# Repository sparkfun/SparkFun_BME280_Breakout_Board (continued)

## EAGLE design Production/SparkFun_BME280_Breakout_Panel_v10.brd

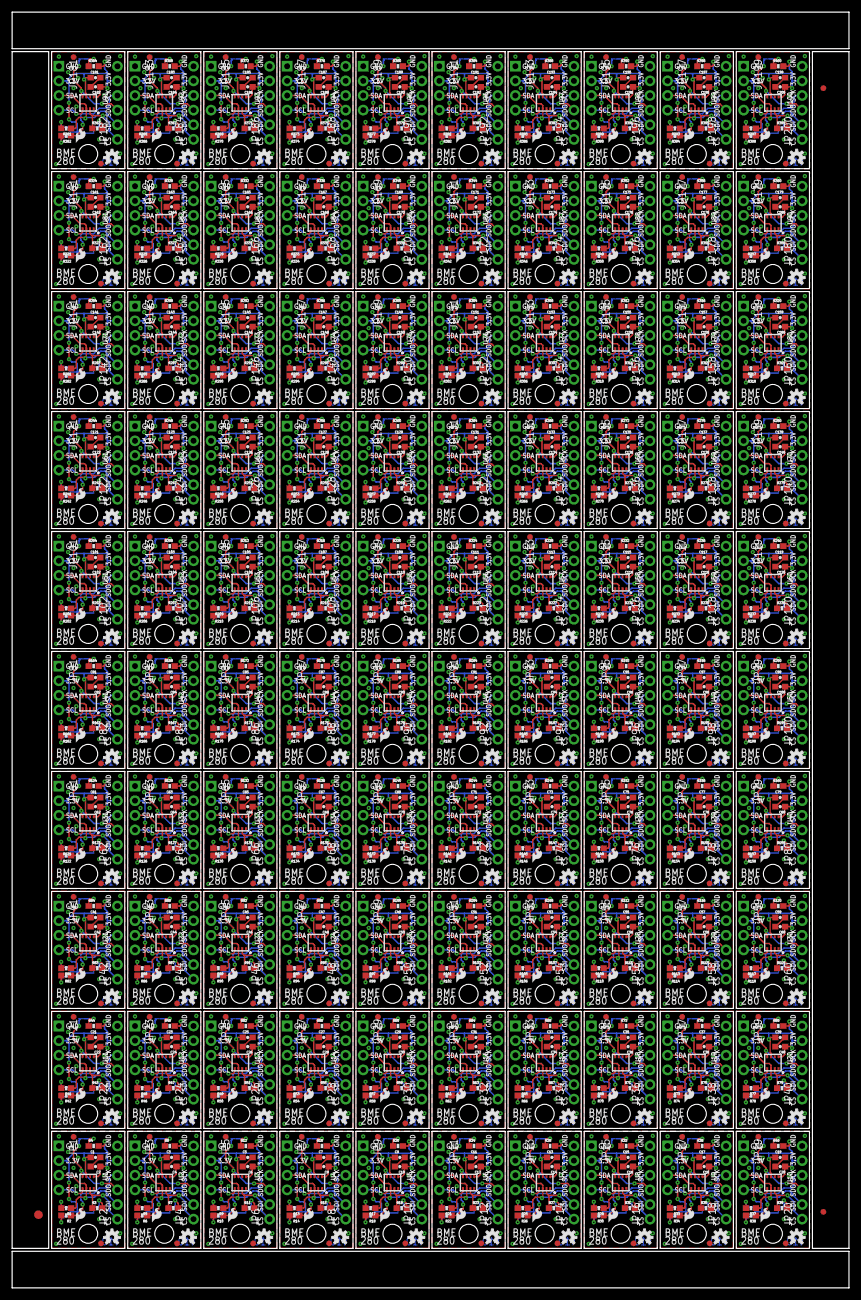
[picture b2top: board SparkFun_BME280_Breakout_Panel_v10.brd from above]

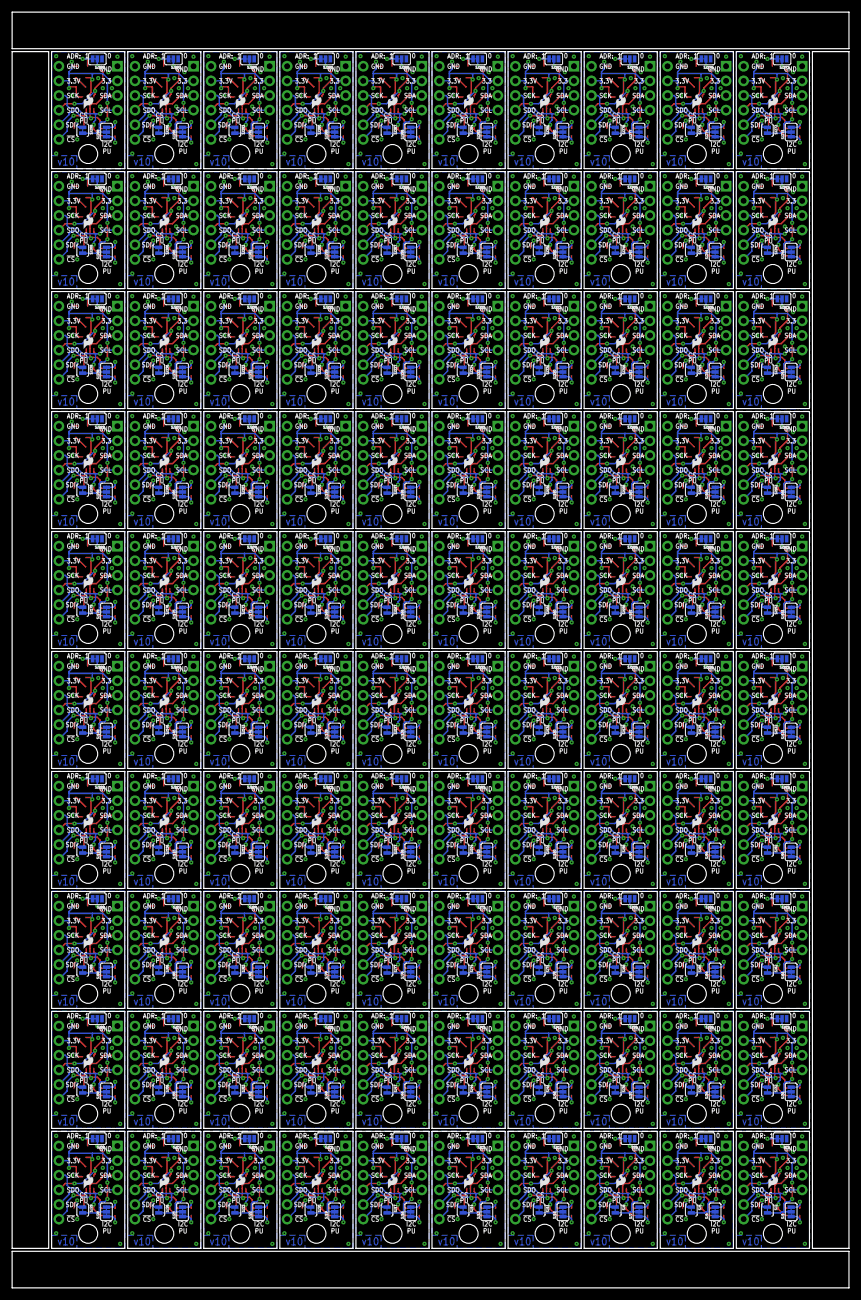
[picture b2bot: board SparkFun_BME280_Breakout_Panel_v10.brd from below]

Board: 2 copper layers, 145.3 x 221.5 mm, 1803 parts (400 on the bottom side), 1000 nets.

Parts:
C1, C2, C3, C4, C5, C6, C7, C8, C9, C10, C11, C12, C13, C14, C15, C16, C17, C18, C19, C20, C21, C22, C23, C24, C25, C26, C27, C28, C29, C30, C31, C32, C33, C34, C35, C36, C37, C38, C39, C40, C41, C42, C43, C44, C45, C46, C47, C48, C49, C50, C51, C52, C53, C54, C55, C56, C57, C58, C59, C60, C61, C62, C63, C64, C65, C66, C67, C68, C69, C70, C71, C72, C73, C74, C75, C76, C77, C78, C79, C80, C81, C82, C83, C84, C85, C86, C87, C88, C89, C90, C91, C92, C93, C94, C95, C96, C97, C98, C99, C100, C101, C102, C103, C104, C105, C106, C107, C108, C109, C110, C111, C112, C113, C114, C115, C116, C117, C118, C119, C120, C121, C122, C123, C124, C125, C126, C127, C128, C129, C130, C131, C132, C133, C134, C135, C136, C137, C138, C139, C140, C141, C142, C143, C144, C145, C146, C147, C148, C149, C150, C151, C152, C153, C154, C155, C156, C157, C158, C159, C160, C161, C162, C163, C164, C165, C166, C167, C168, C169, C170, C171, C172, C173, C174, C175, C176, C177, C178, C179, C180, C181, C182, C183, C184, C185, C186, C187, C188, C189, C190, C191, C192, C193, C194, C195, C196, C197, C198, C199, C200: 0.1uF; 0603-CAP
E$1: FIDUCIAL-1.5X3
E$5, E$6: FIDUCIAL-1X2
FID1, FID2, FID3, FID4, FID5, FID6, FID7, FID8, FID9, FID10, FID11, FID12, FID13, FID14, FID15, FID16, FID17, FID18, FID19, FID20, FID21, FID22, FID23, FID24, FID25, FID26, FID27, FID28, FID29, FID30, FID31, FID32, FID33, FID34, FID35, FID36, FID37, FID38, FID39, FID40, FID41, FID42, FID43, FID44, FID45, FID46, FID47, FID48, FID49, FID50, FID51, FID52, FID53, FID54, FID55, FID56, FID57, FID58, FID59, FID60, FID61, FID62, FID63, FID64, FID65, FID66, FID67, FID68, FID69, FID70, FID71, FID72, FID73, FID74, FID75, FID76, FID77, FID78, FID79, FID80, FID81, FID82, FID83, FID84, FID85, FID86, FID87, FID88, FID89, FID90, FID91, FID92, FID93, FID94, FID95, FID96, FID97, FID98, FID99, FID100, FID101, FID102, FID103, FID104, FID105, FID106, FID107, FID108, FID109, FID110, FID111, FID112, FID113, FID114, FID115, FID116, FID117, FID118, FID119, FID120, FID121, FID122, FID123, FID124, FID125, FID126, FID127, FID128, FID129, FID130, FID131, FID132, FID133, FID134, FID135, FID136, FID137, FID138, FID139, FID140, FID141, FID142, FID143, FID144, FID145, FID146, FID147, FID148, FID149, FID150, FID151, FID152, FID153, FID154, FID155, FID156, FID157, FID158, FID159, FID160, FID161, FID162, FID163, FID164, FID165, FID166, FID167, FID168, FID169, FID170, FID171, FID172, FID173, FID174, FID175, FID176, FID177, FID178, FID179, FID180, FID181, FID182, FID183, FID184, FID185, FID186, FID187, FID188, FID189, FID190, FID191, FID192, FID193, FID194, FID195, FID196, FID197, FID198, FID199, FID200: FIDUCIAL1X2; FIDUCIAL-1X2
JP1, JP3, JP5, JP7, JP9, JP11, JP13, JP15, JP17, JP19, JP21, JP23, JP25, JP27, JP29, JP31, JP33, JP35, JP37, JP39, JP41, JP43, JP45, JP47, JP49, JP51, JP53, JP55, JP57, JP59, JP61, JP63, JP65, JP67, JP69, JP71, JP73, JP75, JP77, JP79, JP81, JP83, JP85, JP87, JP89, JP91, JP93, JP95, JP97, JP99, JP101, JP103, JP105, JP107, JP109, JP111, JP113, JP115, JP117, JP119, JP121, JP123, JP125, JP127, JP129, JP131, JP133, JP135, JP137, JP139, JP141, JP143, JP145, JP147, JP149, JP151, JP153, JP155, JP157, JP159, JP161, JP163, JP165, JP167, JP169, JP171, JP173, JP175, JP177, JP179, JP181, JP183, JP185, JP187, JP189, JP191, JP193, JP195, JP197, JP199: 1X04_NO_SILK
JP2, JP4, JP6, JP8, JP10, JP12, JP14, JP16, JP18, JP20, JP22, JP24, JP26, JP28, JP30, JP32, JP34, JP36, JP38, JP40, JP42, JP44, JP46, JP48, JP50, JP52, JP54, JP56, JP58, JP60, JP62, JP64, JP66, JP68, JP70, JP72, JP74, JP76, JP78, JP80, JP82, JP84, JP86, JP88, JP90, JP92, JP94, JP96, JP98, JP100, JP102, JP104, JP106, JP108, JP110, JP112, JP114, JP116, JP118, JP120, JP122, JP124, JP126, JP128, JP130, JP132, JP134, JP136, JP138, JP140, JP142, JP144, JP146, JP148, JP150, JP152, JP154, JP156, JP158, JP160, JP162, JP164, JP166, JP168, JP170, JP172, JP174, JP176, JP178, JP180, JP182, JP184, JP186, JP188, JP190, JP192, JP194, JP196, JP198, JP200: 1X06_NO_SILK
LOGO1, LOGO2, LOGO4, LOGO5, LOGO7, LOGO8, LOGO10, LOGO11, LOGO13, LOGO14, LOGO16, LOGO17, LOGO19, LOGO20, LOGO22, LOGO23, LOGO25, LOGO26, LOGO28, LOGO29, LOGO31, LOGO32, LOGO34, LOGO35, LOGO37, LOGO38, LOGO40, LOGO41, LOGO43, LOGO44, LOGO46, LOGO47, LOGO49, LOGO50, LOGO52, LOGO53, LOGO55, LOGO56, LOGO58, LOGO59, LOGO61, LOGO62, LOGO64, LOGO65, LOGO67, LOGO68, LOGO70, LOGO71, LOGO73, LOGO74, LOGO76, LOGO77, LOGO79, LOGO80, LOGO82, LOGO83, LOGO85, LOGO86, LOGO88, LOGO89, LOGO91, LOGO92, LOGO94, LOGO95, LOGO97, LOGO98, LOGO100, LOGO101, LOGO103, LOGO104, LOGO106, LOGO107, LOGO109, LOGO110, LOGO112, LOGO113, LOGO115, LOGO116, LOGO118, LOGO119, LOGO121, LOGO122, LOGO124, LOGO125, LOGO127, LOGO128, LOGO130, LOGO131, LOGO133, LOGO134, LOGO136, LOGO137, LOGO139, LOGO140, LOGO142, LOGO143, LOGO145, LOGO146, LOGO148, LOGO149, LOGO151, LOGO152, LOGO154, LOGO155, LOGO157, LOGO158, LOGO160, LOGO161, LOGO163, LOGO164, LOGO166, LOGO167, LOGO169, LOGO170, LOGO172, LOGO173, LOGO175, LOGO176, LOGO178, LOGO179, LOGO181, LOGO182, LOGO184, LOGO185, LOGO187, LOGO188, LOGO190, LOGO191, LOGO193, LOGO194, LOGO196, LOGO197, LOGO199, LOGO200, LOGO202, LOGO203, LOGO205, LOGO206, LOGO208, LOGO209, LOGO211, LOGO212, LOGO214, LOGO215, LOGO217, LOGO218, LOGO220, LOGO221, LOGO223, LOGO224, LOGO226, LOGO227, LOGO229, LOGO230, LOGO232, LOGO233, LOGO235, LOGO236, LOGO238, LOGO239, LOGO241, LOGO242, LOGO244, LOGO245, LOGO247, LOGO248, LOGO250, LOGO251, LOGO253, LOGO254, LOGO256, LOGO257, LOGO259, LOGO260, LOGO262, LOGO263, LOGO265, LOGO266, LOGO268, LOGO269, LOGO271, LOGO272, LOGO274, LOGO275, LOGO277, LOGO278, LOGO280, LOGO281, LOGO283, LOGO284, LOGO286, LOGO287, LOGO289, LOGO290, LOGO292, LOGO293, LOGO295, LOGO296, LOGO298, LOGO299: SFE_LOGO_FLAME.1_INCH; SFE_LOGO_FLAME_.1
LOGO3, LOGO6, LOGO9, LOGO12, LOGO15, LOGO18, LOGO21, LOGO24, LOGO27, LOGO30, LOGO33, LOGO36, LOGO39, LOGO42, LOGO45, LOGO48, LOGO51, LOGO54, LOGO57, LOGO60, LOGO63, LOGO66, LOGO69, LOGO72, LOGO75, LOGO78, LOGO81, LOGO84, LOGO87, LOGO90, LOGO93, LOGO96, LOGO99, LOGO102, LOGO105, LOGO108, LOGO111, LOGO114, LOGO117, LOGO120, LOGO123, LOGO126, LOGO129, LOGO132, LOGO135, LOGO138, LOGO141, LOGO144, LOGO147, LOGO150, LOGO153, LOGO156, LOGO159, LOGO162, LOGO165, LOGO168, LOGO171, LOGO174, LOGO177, LOGO180, LOGO183, LOGO186, LOGO189, LOGO192, LOGO195, LOGO198, LOGO201, LOGO204, LOGO207, LOGO210, LOGO213, LOGO216, LOGO219, LOGO222, LOGO225, LOGO228, LOGO231, LOGO234, LOGO237, LOGO240, LOGO243, LOGO246, LOGO249, LOGO252, LOGO255, LOGO258, LOGO261, LOGO264, LOGO267, LOGO270, LOGO273, LOGO276, LOGO279, LOGO282, LOGO285, LOGO288, LOGO291, LOGO294, LOGO297, LOGO300: OSHW-LOGOS; OSHW-LOGO-S
R1, R2, R3, R4, R5, R6, R7, R8, R9, R10, R11, R12, R13, R14, R15, R16, R17, R18, R19, R20, R21, R22, R23, R24, R25, R26, R27, R28, R29, R30, R31, R32, R33, R34, R35, R36, R37, R38, R39, R40, R41, R42, R43, R44, R45, R46, R47, R48, R49, R50, R51, R52, R53, R54, R55, R56, R57, R58, R59, R60, R61, R62, R63, R64, R65, R66, R67, R68, R69, R70, R71, R72, R73, R74, R75, R76, R77, R78, R79, R80, R81, R82, R83, R84, R85, R86, R87, R88, R89, R90, R91, R92, R93, R94, R95, R96, R97, R98, R99, R100, R101, R102, R103, R104, R105, R106, R107, R108, R109, R110, R111, R112, R113, R114, R115, R116, R117, R118, R119, R120, R121, R122, R123, R124, R125, R126, R127, R128, R129, R130, R131, R132, R133, R134, R135, R136, R137, R138, R139, R140, R141, R142, R143, R144, R145, R146, R147, R148, R149, R150, R151, R152, R153, R154, R155, R156, R157, R158, R159, R160, R161, R162, R163, R164, R165, R166, R167, R168, R169, R170, R171, R172, R173, R174, R175, R176, R177, R178, R179, R180, R181, R182, R183, R184, R185, R186, R187, R188, R189, R190, R191, R192, R193, R194, R195, R196, R197, R198, R199, R200, R201, R202, R203, R204, R205, R206, R207, R208, R209, R210, R211, R212, R213, R214, R215, R216, R217, R218, R219, R220, R221, R222, R223, R224, R225, R226, R227, R228, R229, R230, R231, R232, R233, R234, R235, R236, R237, R238, R239, R240, R241, R242, R243, R244, R245, R246, R247, R248, R249, R250, R251, R252, R253, R254, R255, R256, R257, R258, R259, R260, R261, R262, R263, R264, R265, R266, R267, R268, R269, R270, R271, R272, R273, R274, R275, R276, R277, R278, R279, R280, R281, R282, R283, R284, R285, R286, R287, R288, R289, R290, R291, R292, R293, R294, R295, R296, R297, R298, R299, R300, R301, R302, R303, R304, R305, R306, R307, R308, R309, R310, R311, R312, R313, R314, R315, R316, R317, R318, R319, R320, R321, R322, R323, R324, R325, R326, R327, R328, R329, R330, R331, R332, R333, R334, R335, R336, R337, R338, R339, R340, R341, R342, R343, R344, R345, R346, R347, R348, R349, R350, R351, R352, R353, R354, R355, R356, R357, R358, R359, R360, R361, R362, R363, R364, R365, R366, R367, R368, R369, R370, R371, R372, R373, R374, R375, R376, R377, R378, R379, R380, R381, R382, R383, R384, R385, R386, R387, R388, R389, R390, R391, R392, R393, R394, R395, R396, R397, R398, R399, R400: 4.7K; 0603-RES
SJ1, SJ4, SJ7, SJ10, SJ13, SJ16, SJ19, SJ22, SJ25, SJ28, SJ31, SJ34, SJ37, SJ40, SJ43, SJ46, SJ49, SJ52, SJ55, SJ58, SJ61, SJ64, SJ67, SJ70, SJ73, SJ76, SJ79, SJ82, SJ85, SJ88, SJ91, SJ94, SJ97, SJ100, SJ103, SJ106, SJ109, SJ112, SJ115, SJ118, SJ121, SJ124, SJ127, SJ130, SJ133, SJ136, SJ139, SJ142, SJ145, SJ148, SJ151, SJ154, SJ157, SJ160, SJ163, SJ166, SJ169, SJ172, SJ175, SJ178, SJ181, SJ184, SJ187, SJ190, SJ193, SJ196, SJ199, SJ202, SJ205, SJ208, SJ211, SJ214, SJ217, SJ220, SJ223, SJ226, SJ229, SJ232, SJ235, SJ238, SJ241, SJ244, SJ247, SJ250, SJ253, SJ256, SJ259, SJ262, SJ265, SJ268, SJ271, SJ274, SJ277, SJ280, SJ283, SJ286, SJ289, SJ292, SJ295, SJ298: EN I2C PULL; PAD-JUMPER-3-3OF3_NC_BY_TRACE_YES_SILK_FULL_BOX
SJ2, SJ5, SJ8, SJ11, SJ14, SJ17, SJ20, SJ23, SJ26, SJ29, SJ32, SJ35, SJ38, SJ41, SJ44, SJ47, SJ50, SJ53, SJ56, SJ59, SJ62, SJ65, SJ68, SJ71, SJ74, SJ77, SJ80, SJ83, SJ86, SJ89, SJ92, SJ95, SJ98, SJ101, SJ104, SJ107, SJ110, SJ113, SJ116, SJ119, SJ122, SJ125, SJ128, SJ131, SJ134, SJ137, SJ140, SJ143, SJ146, SJ149, SJ152, SJ155, SJ158, SJ161, SJ164, SJ167, SJ170, SJ173, SJ176, SJ179, SJ182, SJ185, SJ188, SJ191, SJ194, SJ197, SJ200, SJ203, SJ206, SJ209, SJ212, SJ215, SJ218, SJ221, SJ224, SJ227, SJ230, SJ233, SJ236, SJ239, SJ242, SJ245, SJ248, SJ251, SJ254, SJ257, SJ260, SJ263, SJ266, SJ269, SJ272, SJ275, SJ278, SJ281, SJ284, SJ287, SJ290, SJ293, SJ296, SJ299: EN I2C MODE; PAD-JUMPER-2-NC_BY_TRACE_YES_SILK
SJ3, SJ6, SJ9, SJ12, SJ15, SJ18, SJ21, SJ24, SJ27, SJ30, SJ33, SJ36, SJ39, SJ42, SJ45, SJ48, SJ51, SJ54, SJ57, SJ60, SJ63, SJ66, SJ69, SJ72, SJ75, SJ78, SJ81, SJ84, SJ87, SJ90, SJ93, SJ96, SJ99, SJ102, SJ105, SJ108, SJ111, SJ114, SJ117, SJ120, SJ123, SJ126, SJ129, SJ132, SJ135, SJ138, SJ141, SJ144, SJ147, SJ150, SJ153, SJ156, SJ159, SJ162, SJ165, SJ168, SJ171, SJ174, SJ177, SJ180, SJ183, SJ186, SJ189, SJ192, SJ195, SJ198, SJ201, SJ204, SJ207, SJ210, SJ213, SJ216, SJ219, SJ222, SJ225, SJ228, SJ231, SJ234, SJ237, SJ240, SJ243, SJ246, SJ249, SJ252, SJ255, SJ258, SJ261, SJ264, SJ267, SJ270, SJ273, SJ276, SJ279, SJ282, SJ285, SJ288, SJ291, SJ294, SJ297, SJ300: EN ADR PULLUP; PAD-JUMPER-3-2OF3_NC_BY_TRACE_YES_SILK_FULL_BOX
STANDOFF1, STANDOFF2, STANDOFF3, STANDOFF4, STANDOFF5, STANDOFF6, STANDOFF7, STANDOFF8, STANDOFF9, STANDOFF10, STANDOFF11, STANDOFF12, STANDOFF13, STANDOFF14, STANDOFF15, STANDOFF16, STANDOFF17, STANDOFF18, STANDOFF19, STANDOFF20, STANDOFF21, STANDOFF22, STANDOFF23, STANDOFF24, STANDOFF25, STANDOFF26, STANDOFF27, STANDOFF28, STANDOFF29, STANDOFF30, STANDOFF31, STANDOFF32, STANDOFF33, STANDOFF34, STANDOFF35, STANDOFF36, STANDOFF37, STANDOFF38, STANDOFF39, STANDOFF40, STANDOFF41, STANDOFF42, STANDOFF43, STANDOFF44, STANDOFF45, STANDOFF46, STANDOFF47, STANDOFF48, STANDOFF49, STANDOFF50, STANDOFF51, STANDOFF52, STANDOFF53, STANDOFF54, STANDOFF55, STANDOFF56, STANDOFF57, STANDOFF58, STANDOFF59, STANDOFF60, STANDOFF61, STANDOFF62, STANDOFF63, STANDOFF64, STANDOFF65, STANDOFF66, STANDOFF67, STANDOFF68, STANDOFF69, STANDOFF70, STANDOFF71, STANDOFF72, STANDOFF73, STANDOFF74, STANDOFF75, STANDOFF76, STANDOFF77, STANDOFF78, STANDOFF79, STANDOFF80, STANDOFF81, STANDOFF82, STANDOFF83, STANDOFF84, STANDOFF85, STANDOFF86, STANDOFF87, STANDOFF88, STANDOFF89, STANDOFF90, STANDOFF91, STANDOFF92, STANDOFF93, STANDOFF94, STANDOFF95, STANDOFF96, STANDOFF97, STANDOFF98, STANDOFF99, STANDOFF100: STAND-OFF
U1, U2, U3, U4, U5, U6, U7, U8, U9, U10, U11, U12, U13, U14, U15, U16, U17, U18, U19, U20, U21, U22, U23, U24, U25, U26, U27, U28, U29, U30, U31, U32, U33, U34, U35, U36, U37, U38, U39, U40, U41, U42, U43, U44, U45, U46, U47, U48, U49, U50, U51, U52, U53, U54, U55, U56, U57, U58, U59, U60, U61, U62, U63, U64, U65, U66, U67, U68, U69, U70, U71, U72, U73, U74, U75, U76, U77, U78, U79, U80, U81, U82, U83, U84, U85, U86, U87, U88, U89, U90, U91, U92, U93, U94, U95, U96, U97, U98, U99, U100: BME280; BME280_LGA

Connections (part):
3.3V: C1.1, C2.1, JP1.2, JP2.5, R4.2, SJ1.2, SJ2.2, U1.P$6, U1.P$8
3.3V1: C3.1, C4.1, JP3.2, JP4.5, R8.2, SJ4.2, SJ5.2, U2.P$6, U2.P$8
3.3V2: C5.1, C6.1, JP5.2, JP6.5, R12.2, SJ7.2, SJ8.2, U3.P$6, U3.P$8
3.3V3: C7.1, C8.1, JP7.2, JP8.5, R16.2, SJ10.2, SJ11.2, U4.P$6, U4.P$8
3.3V4: C9.1, C10.1, JP9.2, JP10.5, R20.2, SJ13.2, SJ14.2, U5.P$6, U5.P$8
3.3V5: C11.1, C12.1, JP11.2, JP12.5, R24.2, SJ16.2, SJ17.2, U6.P$6, U6.P$8
3.3V6: C13.1, C14.1, JP13.2, JP14.5, R28.2, SJ19.2, SJ20.2, U7.P$6, U7.P$8
3.3V7: C15.1, C16.1, JP15.2, JP16.5, R32.2, SJ22.2, SJ23.2, U8.P$6, U8.P$8
3.3V8: C17.1, C18.1, JP17.2, JP18.5, R36.2, SJ25.2, SJ26.2, U9.P$6, U9.P$8
3.3V9: C19.1, C20.1, JP19.2, JP20.5, R40.2, SJ28.2, SJ29.2, U10.P$6, U10.P$8
3.3V10: C21.1, C22.1, JP21.2, JP22.5, R44.2, SJ31.2, SJ32.2, U11.P$6, U11.P$8
3.3V11: C23.1, C24.1, JP23.2, JP24.5, R48.2, SJ34.2, SJ35.2, U12.P$6, U12.P$8
3.3V12: C25.1, C26.1, JP25.2, JP26.5, R52.2, SJ37.2, SJ38.2, U13.P$6, U13.P$8
3.3V13: C27.1, C28.1, JP27.2, JP28.5, R56.2, SJ40.2, SJ41.2, U14.P$6, U14.P$8
3.3V14: C29.1, C30.1, JP29.2, JP30.5, R60.2, SJ43.2, SJ44.2, U15.P$6, U15.P$8
3.3V15: C31.1, C32.1, JP31.2, JP32.5, R64.2, SJ46.2, SJ47.2, U16.P$6, U16.P$8
3.3V16: C33.1, C34.1, JP33.2, JP34.5, R68.2, SJ49.2, SJ50.2, U17.P$6, U17.P$8
3.3V17: C35.1, C36.1, JP35.2, JP36.5, R72.2, SJ52.2, SJ53.2, U18.P$6, U18.P$8
3.3V18: C37.1, C38.1, JP37.2, JP38.5, R76.2, SJ55.2, SJ56.2, U19.P$6, U19.P$8
3.3V19: C39.1, C40.1, JP39.2, JP40.5, R80.2, SJ58.2, SJ59.2, U20.P$6, U20.P$8
3.3V20: C41.1, C42.1, JP41.2, JP42.5, R84.2, SJ61.2, SJ62.2, U21.P$6, U21.P$8
3.3V21: C43.1, C44.1, JP43.2, JP44.5, R88.2, SJ64.2, SJ65.2, U22.P$6, U22.P$8
3.3V22: C45.1, C46.1, JP45.2, JP46.5, R92.2, SJ67.2, SJ68.2, U23.P$6, U23.P$8
3.3V23: C47.1, C48.1, JP47.2, JP48.5, R96.2, SJ70.2, SJ71.2, U24.P$6, U24.P$8
3.3V24: C49.1, C50.1, JP49.2, JP50.5, R100.2, SJ73.2, SJ74.2, U25.P$6, U25.P$8
3.3V25: C51.1, C52.1, JP51.2, JP52.5, R104.2, SJ76.2, SJ77.2, U26.P$6, U26.P$8
3.3V26: C53.1, C54.1, JP53.2, JP54.5, R108.2, SJ79.2, SJ80.2, U27.P$6, U27.P$8
3.3V27: C55.1, C56.1, JP55.2, JP56.5, R112.2, SJ82.2, SJ83.2, U28.P$6, U28.P$8
3.3V28: C57.1, C58.1, JP57.2, JP58.5, R116.2, SJ85.2, SJ86.2, U29.P$6, U29.P$8
3.3V29: C59.1, C60.1, JP59.2, JP60.5, R120.2, SJ88.2, SJ89.2, U30.P$6, U30.P$8
3.3V30: C61.1, C62.1, JP61.2, JP62.5, R124.2, SJ91.2, SJ92.2, U31.P$6, U31.P$8
3.3V31: C63.1, C64.1, JP63.2, JP64.5, R128.2, SJ94.2, SJ95.2, U32.P$6, U32.P$8
3.3V32: C65.1, C66.1, JP65.2, JP66.5, R132.2, SJ97.2, SJ98.2, U33.P$6, U33.P$8
3.3V33: C67.1, C68.1, JP67.2, JP68.5, R136.2, SJ100.2, SJ101.2, U34.P$6, U34.P$8
3.3V34: C69.1, C70.1, JP69.2, JP70.5, R140.2, SJ103.2, SJ104.2, U35.P$6, U35.P$8
3.3V35: C71.1, C72.1, JP71.2, JP72.5, R144.2, SJ106.2, SJ107.2, U36.P$6, U36.P$8
3.3V36: C73.1, C74.1, JP73.2, JP74.5, R148.2, SJ109.2, SJ110.2, U37.P$6, U37.P$8
3.3V37: C75.1, C76.1, JP75.2, JP76.5, R152.2, SJ112.2, SJ113.2, U38.P$6, U38.P$8
3.3V38: C77.1, C78.1, JP77.2, JP78.5, R156.2, SJ115.2, SJ116.2, U39.P$6, U39.P$8
3.3V39: C79.1, C80.1, JP79.2, JP80.5, R160.2, SJ118.2, SJ119.2, U40.P$6, U40.P$8
3.3V40: C81.1, C82.1, JP81.2, JP82.5, R164.2, SJ121.2, SJ122.2, U41.P$6, U41.P$8
3.3V41: C83.1, C84.1, JP83.2, JP84.5, R168.2, SJ124.2, SJ125.2, U42.P$6, U42.P$8
3.3V42: C85.1, C86.1, JP85.2, JP86.5, R172.2, SJ127.2, SJ128.2, U43.P$6, U43.P$8
3.3V43: C87.1, C88.1, JP87.2, JP88.5, R176.2, SJ130.2, SJ131.2, U44.P$6, U44.P$8
3.3V44: C89.1, C90.1, JP89.2, JP90.5, R180.2, SJ133.2, SJ134.2, U45.P$6, U45.P$8
3.3V45: C91.1, C92.1, JP91.2, JP92.5, R184.2, SJ136.2, SJ137.2, U46.P$6, U46.P$8
3.3V46: C93.1, C94.1, JP93.2, JP94.5, R188.2, SJ139.2, SJ140.2, U47.P$6, U47.P$8
3.3V47: C95.1, C96.1, JP95.2, JP96.5, R192.2, SJ142.2, SJ143.2, U48.P$6, U48.P$8
3.3V48: C97.1, C98.1, JP97.2, JP98.5, R196.2, SJ145.2, SJ146.2, U49.P$6, U49.P$8
3.3V49: C99.1, C100.1, JP99.2, JP100.5, R200.2, SJ148.2, SJ149.2, U50.P$6, U50.P$8
3.3V50: C101.1, C102.1, JP101.2, JP102.5, R204.2, SJ151.2, SJ152.2, U51.P$6, U51.P$8
3.3V51: C103.1, C104.1, JP103.2, JP104.5, R208.2, SJ154.2, SJ155.2, U52.P$6, U52.P$8
3.3V52: C105.1, C106.1, JP105.2, JP106.5, R212.2, SJ157.2, SJ158.2, U53.P$6, U53.P$8
3.3V53: C107.1, C108.1, JP107.2, JP108.5, R216.2, SJ160.2, SJ161.2, U54.P$6, U54.P$8
3.3V54: C109.1, C110.1, JP109.2, JP110.5, R220.2, SJ163.2, SJ164.2, U55.P$6, U55.P$8
3.3V55: C111.1, C112.1, JP111.2, JP112.5, R224.2, SJ166.2, SJ167.2, U56.P$6, U56.P$8
3.3V56: C113.1, C114.1, JP113.2, JP114.5, R228.2, SJ169.2, SJ170.2, U57.P$6, U57.P$8
3.3V57: C115.1, C116.1, JP115.2, JP116.5, R232.2, SJ172.2, SJ173.2, U58.P$6, U58.P$8
3.3V58: C117.1, C118.1, JP117.2, JP118.5, R236.2, SJ175.2, SJ176.2, U59.P$6, U59.P$8
3.3V59: C119.1, C120.1, JP119.2, JP120.5, R240.2, SJ178.2, SJ179.2, U60.P$6, U60.P$8
3.3V60: C121.1, C122.1, JP121.2, JP122.5, R244.2, SJ181.2, SJ182.2, U61.P$6, U61.P$8
3.3V61: C123.1, C124.1, JP123.2, JP124.5, R248.2, SJ184.2, SJ185.2, U62.P$6, U62.P$8
3.3V62: C125.1, C126.1, JP125.2, JP126.5, R252.2, SJ187.2, SJ188.2, U63.P$6, U63.P$8
3.3V63: C127.1, C128.1, JP127.2, JP128.5, R256.2, SJ190.2, SJ191.2, U64.P$6, U64.P$8
3.3V64: C129.1, C130.1, JP129.2, JP130.5, R260.2, SJ193.2, SJ194.2, U65.P$6, U65.P$8
3.3V65: C131.1, C132.1, JP131.2, JP132.5, R264.2, SJ196.2, SJ197.2, U66.P$6, U66.P$8
3.3V66: C133.1, C134.1, JP133.2, JP134.5, R268.2, SJ199.2, SJ200.2, U67.P$6, U67.P$8
3.3V67: C135.1, C136.1, JP135.2, JP136.5, R272.2, SJ202.2, SJ203.2, U68.P$6, U68.P$8
3.3V68: C137.1, C138.1, JP137.2, JP138.5, R276.2, SJ205.2, SJ206.2, U69.P$6, U69.P$8
3.3V69: C139.1, C140.1, JP139.2, JP140.5, R280.2, SJ208.2, SJ209.2, U70.P$6, U70.P$8
3.3V70: C141.1, C142.1, JP141.2, JP142.5, R284.2, SJ211.2, SJ212.2, U71.P$6, U71.P$8
3.3V71: C143.1, C144.1, JP143.2, JP144.5, R288.2, SJ214.2, SJ215.2, U72.P$6, U72.P$8
3.3V72: C145.1, C146.1, JP145.2, JP146.5, R292.2, SJ217.2, SJ218.2, U73.P$6, U73.P$8
3.3V73: C147.1, C148.1, JP147.2, JP148.5, R296.2, SJ220.2, SJ221.2, U74.P$6, U74.P$8
3.3V74: C149.1, C150.1, JP149.2, JP150.5, R300.2, SJ223.2, SJ224.2, U75.P$6, U75.P$8
3.3V75: C151.1, C152.1, JP151.2, JP152.5, R304.2, SJ226.2, SJ227.2, U76.P$6, U76.P$8
3.3V76: C153.1, C154.1, JP153.2, JP154.5, R308.2, SJ229.2, SJ230.2, U77.P$6, U77.P$8
3.3V77: C155.1, C156.1, JP155.2, JP156.5, R312.2, SJ232.2, SJ233.2, U78.P$6, U78.P$8
3.3V78: C157.1, C158.1, JP157.2, JP158.5, R316.2, SJ235.2, SJ236.2, U79.P$6, U79.P$8
3.3V79: C159.1, C160.1, JP159.2, JP160.5, R320.2, SJ238.2, SJ239.2, U80.P$6, U80.P$8
3.3V80: C161.1, C162.1, JP161.2, JP162.5, R324.2, SJ241.2, SJ242.2, U81.P$6, U81.P$8
3.3V81: C163.1, C164.1, JP163.2, JP164.5, R328.2, SJ244.2, SJ245.2, U82.P$6, U82.P$8
3.3V82: C165.1, C166.1, JP165.2, JP166.5, R332.2, SJ247.2, SJ248.2, U83.P$6, U83.P$8
3.3V83: C167.1, C168.1, JP167.2, JP168.5, R336.2, SJ250.2, SJ251.2, U84.P$6, U84.P$8
3.3V84: C169.1, C170.1, JP169.2, JP170.5, R340.2, SJ253.2, SJ254.2, U85.P$6, U85.P$8
3.3V85: C171.1, C172.1, JP171.2, JP172.5, R344.2, SJ256.2, SJ257.2, U86.P$6, U86.P$8
3.3V86: C173.1, C174.1, JP173.2, JP174.5, R348.2, SJ259.2, SJ260.2, U87.P$6, U87.P$8
3.3V87: C175.1, C176.1, JP175.2, JP176.5, R352.2, SJ262.2, SJ263.2, U88.P$6, U88.P$8
3.3V88: C177.1, C178.1, JP177.2, JP178.5, R356.2, SJ265.2, SJ266.2, U89.P$6, U89.P$8
3.3V89: C179.1, C180.1, JP179.2, JP180.5, R360.2, SJ268.2, SJ269.2, U90.P$6, U90.P$8
3.3V90: C181.1, C182.1, JP181.2, JP182.5, R364.2, SJ271.2, SJ272.2, U91.P$6, U91.P$8
3.3V91: C183.1, C184.1, JP183.2, JP184.5, R368.2, SJ274.2, SJ275.2, U92.P$6, U92.P$8
3.3V92: C185.1, C186.1, JP185.2, JP186.5, R372.2, SJ277.2, SJ278.2, U93.P$6, U93.P$8
3.3V93: C187.1, C188.1, JP187.2, JP188.5, R376.2, SJ280.2, SJ281.2, U94.P$6, U94.P$8
3.3V94: C189.1, C190.1, JP189.2, JP190.5, R380.2, SJ283.2, SJ284.2, U95.P$6, U95.P$8
3.3V95: C191.1, C192.1, JP191.2, JP192.5, R384.2, SJ286.2, SJ287.2, U96.P$6, U96.P$8
3.3V96: C193.1, C194.1, JP193.2, JP194.5, R388.2, SJ289.2, SJ290.2, U97.P$6, U97.P$8
3.3V97: C195.1, C196.1, JP195.2, JP196.5, R392.2, SJ292.2, SJ293.2, U98.P$6, U98.P$8
3.3V98: C197.1, C198.1, JP197.2, JP198.5, R396.2, SJ295.2, SJ296.2, U99.P$6, U99.P$8
3.3V99: C199.1, C200.1, JP199.2, JP200.5, R400.2, SJ298.2, SJ299.2, U100.P$6, U100.P$8
!CS: JP2.1, R3.1, U1.P$2
!CS1: JP4.1, R7.1, U2.P$2
!CS2: JP6.1, R11.1, U3.P$2
!CS3: JP8.1, R15.1, U4.P$2
!CS4: JP10.1, R19.1, U5.P$2
!CS5: JP12.1, R23.1, U6.P$2
!CS6: JP14.1, R27.1, U7.P$2
!CS7: JP16.1, R31.1, U8.P$2
!CS8: JP18.1, R35.1, U9.P$2
!CS9: JP20.1, R39.1, U10.P$2
!CS10: JP22.1, R43.1, U11.P$2
!CS11: JP24.1, R47.1, U12.P$2
!CS12: JP26.1, R51.1, U13.P$2
!CS13: JP28.1, R55.1, U14.P$2
!CS14: JP30.1, R59.1, U15.P$2
!CS15: JP32.1, R63.1, U16.P$2
!CS16: JP34.1, R67.1, U17.P$2
!CS17: JP36.1, R71.1, U18.P$2
!CS18: JP38.1, R75.1, U19.P$2
!CS19: JP40.1, R79.1, U20.P$2
!CS20: JP42.1, R83.1, U21.P$2
!CS21: JP44.1, R87.1, U22.P$2
!CS22: JP46.1, R91.1, U23.P$2
!CS23: JP48.1, R95.1, U24.P$2
!CS24: JP50.1, R99.1, U25.P$2
!CS25: JP52.1, R103.1, U26.P$2
!CS26: JP54.1, R107.1, U27.P$2
!CS27: JP56.1, R111.1, U28.P$2
!CS28: JP58.1, R115.1, U29.P$2
!CS29: JP60.1, R119.1, U30.P$2
!CS30: JP62.1, R123.1, U31.P$2
!CS31: JP64.1, R127.1, U32.P$2
!CS32: JP66.1, R131.1, U33.P$2
!CS33: JP68.1, R135.1, U34.P$2
!CS34: JP70.1, R139.1, U35.P$2
!CS35: JP72.1, R143.1, U36.P$2
!CS36: JP74.1, R147.1, U37.P$2
!CS37: JP76.1, R151.1, U38.P$2
!CS38: JP78.1, R155.1, U39.P$2
!CS39: JP80.1, R159.1, U40.P$2
!CS40: JP82.1, R163.1, U41.P$2
!CS41: JP84.1, R167.1, U42.P$2
!CS42: JP86.1, R171.1, U43.P$2
!CS43: JP88.1, R175.1, U44.P$2
!CS44: JP90.1, R179.1, U45.P$2
!CS45: JP92.1, R183.1, U46.P$2
!CS46: JP94.1, R187.1, U47.P$2
!CS47: JP96.1, R191.1, U48.P$2
!CS48: JP98.1, R195.1, U49.P$2
!CS49: JP100.1, R199.1, U50.P$2
!CS50: JP102.1, R203.1, U51.P$2
!CS51: JP104.1, R207.1, U52.P$2
!CS52: JP106.1, R211.1, U53.P$2
!CS53: JP108.1, R215.1, U54.P$2
!CS54: JP110.1, R219.1, U55.P$2
!CS55: JP112.1, R223.1, U56.P$2
!CS56: JP114.1, R227.1, U57.P$2
!CS57: JP116.1, R231.1, U58.P$2
!CS58: JP118.1, R235.1, U59.P$2
!CS59: JP120.1, R239.1, U60.P$2
!CS60: JP122.1, R243.1, U61.P$2
!CS61: JP124.1, R247.1, U62.P$2
!CS62: JP126.1, R251.1, U63.P$2
!CS63: JP128.1, R255.1, U64.P$2
!CS64: JP130.1, R259.1, U65.P$2
!CS65: JP132.1, R263.1, U66.P$2
!CS66: JP134.1, R267.1, U67.P$2
!CS67: JP136.1, R271.1, U68.P$2
!CS68: JP138.1, R275.1, U69.P$2
!CS69: JP140.1, R279.1, U70.P$2
!CS70: JP142.1, R283.1, U71.P$2
!CS71: JP144.1, R287.1, U72.P$2
!CS72: JP146.1, R291.1, U73.P$2
!CS73: JP148.1, R295.1, U74.P$2
!CS74: JP150.1, R299.1, U75.P$2
!CS75: JP152.1, R303.1, U76.P$2
!CS76: JP154.1, R307.1, U77.P$2
!CS77: JP156.1, R311.1, U78.P$2
!CS78: JP158.1, R315.1, U79.P$2
!CS79: JP160.1, R319.1, U80.P$2
!CS80: JP162.1, R323.1, U81.P$2
!CS81: JP164.1, R327.1, U82.P$2
!CS82: JP166.1, R331.1, U83.P$2
!CS83: JP168.1, R335.1, U84.P$2
!CS84: JP170.1, R339.1, U85.P$2
!CS85: JP172.1, R343.1, U86.P$2
!CS86: JP174.1, R347.1, U87.P$2
!CS87: JP176.1, R351.1, U88.P$2
!CS88: JP178.1, R355.1, U89.P$2
!CS89: JP180.1, R359.1, U90.P$2
!CS90: JP182.1, R363.1, U91.P$2
!CS91: JP184.1, R367.1, U92.P$2
!CS92: JP186.1, R371.1, U93.P$2
!CS93: JP188.1, R375.1, U94.P$2
!CS94: JP190.1, R379.1, U95.P$2
!CS95: JP192.1, R383.1, U96.P$2
!CS96: JP194.1, R387.1, U97.P$2
!CS97: JP196.1, R391.1, U98.P$2
!CS98: JP198.1, R395.1, U99.P$2
!CS99: JP200.1, R399.1, U100.P$2
GND: C1.2, C2.2, JP1.1, JP2.6, SJ3.1, U1.P$1, U1.P$7
GND1: C3.2, C4.2, JP3.1, JP4.6, SJ6.1, U2.P$1, U2.P$7
GND2: C5.2, C6.2, JP5.1, JP6.6, SJ9.1, U3.P$1, U3.P$7
GND3: C7.2, C8.2, JP7.1, JP8.6, SJ12.1, U4.P$1, U4.P$7
GND4: C9.2, C10.2, JP9.1, JP10.6, SJ15.1, U5.P$1, U5.P$7
GND5: C11.2, C12.2, JP11.1, JP12.6, SJ18.1, U6.P$1, U6.P$7
GND6: C13.2, C14.2, JP13.1, JP14.6, SJ21.1, U7.P$1, U7.P$7
GND7: C15.2, C16.2, JP15.1, JP16.6, SJ24.1, U8.P$1, U8.P$7
GND8: C17.2, C18.2, JP17.1, JP18.6, SJ27.1, U9.P$1, U9.P$7
GND9: C19.2, C20.2, JP19.1, JP20.6, SJ30.1, U10.P$1, U10.P$7
GND10: C21.2, C22.2, JP21.1, JP22.6, SJ33.1, U11.P$1, U11.P$7
GND11: C23.2, C24.2, JP23.1, JP24.6, SJ36.1, U12.P$1, U12.P$7
GND12: C25.2, C26.2, JP25.1, JP26.6, SJ39.1, U13.P$1, U13.P$7
GND13: C27.2, C28.2, JP27.1, JP28.6, SJ42.1, U14.P$1, U14.P$7
GND14: C29.2, C30.2, JP29.1, JP30.6, SJ45.1, U15.P$1, U15.P$7
GND15: C31.2, C32.2, JP31.1, JP32.6, SJ48.1, U16.P$1, U16.P$7
GND16: C33.2, C34.2, JP33.1, JP34.6, SJ51.1, U17.P$1, U17.P$7
GND17: C35.2, C36.2, JP35.1, JP36.6, SJ54.1, U18.P$1, U18.P$7
GND18: C37.2, C38.2, JP37.1, JP38.6, SJ57.1, U19.P$1, U19.P$7
GND19: C39.2, C40.2, JP39.1, JP40.6, SJ60.1, U20.P$1, U20.P$7
GND20: C41.2, C42.2, JP41.1, JP42.6, SJ63.1, U21.P$1, U21.P$7
GND21: C43.2, C44.2, JP43.1, JP44.6, SJ66.1, U22.P$1, U22.P$7
GND22: C45.2, C46.2, JP45.1, JP46.6, SJ69.1, U23.P$1, U23.P$7
GND23: C47.2, C48.2, JP47.1, JP48.6, SJ72.1, U24.P$1, U24.P$7
GND24: C49.2, C50.2, JP49.1, JP50.6, SJ75.1, U25.P$1, U25.P$7
GND25: C51.2, C52.2, JP51.1, JP52.6, SJ78.1, U26.P$1, U26.P$7
GND26: C53.2, C54.2, JP53.1, JP54.6, SJ81.1, U27.P$1, U27.P$7
GND27: C55.2, C56.2, JP55.1, JP56.6, SJ84.1, U28.P$1, U28.P$7
GND28: C57.2, C58.2, JP57.1, JP58.6, SJ87.1, U29.P$1, U29.P$7
GND29: C59.2, C60.2, JP59.1, JP60.6, SJ90.1, U30.P$1, U30.P$7
GND30: C61.2, C62.2, JP61.1, JP62.6, SJ93.1, U31.P$1, U31.P$7
GND31: C63.2, C64.2, JP63.1, JP64.6, SJ96.1, U32.P$1, U32.P$7
GND32: C65.2, C66.2, JP65.1, JP66.6, SJ99.1, U33.P$1, U33.P$7
GND33: C67.2, C68.2, JP67.1, JP68.6, SJ102.1, U34.P$1, U34.P$7
GND34: C69.2, C70.2, JP69.1, JP70.6, SJ105.1, U35.P$1, U35.P$7
GND35: C71.2, C72.2, JP71.1, JP72.6, SJ108.1, U36.P$1, U36.P$7
GND36: C73.2, C74.2, JP73.1, JP74.6, SJ111.1, U37.P$1, U37.P$7
GND37: C75.2, C76.2, JP75.1, JP76.6, SJ114.1, U38.P$1, U38.P$7
GND38: C77.2, C78.2, JP77.1, JP78.6, SJ117.1, U39.P$1, U39.P$7
GND39: C79.2, C80.2, JP79.1, JP80.6, SJ120.1, U40.P$1, U40.P$7
GND40: C81.2, C82.2, JP81.1, JP82.6, SJ123.1, U41.P$1, U41.P$7
GND41: C83.2, C84.2, JP83.1, JP84.6, SJ126.1, U42.P$1, U42.P$7
GND42: C85.2, C86.2, JP85.1, JP86.6, SJ129.1, U43.P$1, U43.P$7
GND43: C87.2, C88.2, JP87.1, JP88.6, SJ132.1, U44.P$1, U44.P$7
GND44: C89.2, C90.2, JP89.1, JP90.6, SJ135.1, U45.P$1, U45.P$7
GND45: C91.2, C92.2, JP91.1, JP92.6, SJ138.1, U46.P$1, U46.P$7
GND46: C93.2, C94.2, JP93.1, JP94.6, SJ141.1, U47.P$1, U47.P$7
GND47: C95.2, C96.2, JP95.1, JP96.6, SJ144.1, U48.P$1, U48.P$7
GND48: C97.2, C98.2, JP97.1, JP98.6, SJ147.1, U49.P$1, U49.P$7
GND49: C99.2, C100.2, JP99.1, JP100.6, SJ150.1, U50.P$1, U50.P$7
GND50: C101.2, C102.2, JP101.1, JP102.6, SJ153.1, U51.P$1, U51.P$7
GND51: C103.2, C104.2, JP103.1, JP104.6, SJ156.1, U52.P$1, U52.P$7
GND52: C105.2, C106.2, JP105.1, JP106.6, SJ159.1, U53.P$1, U53.P$7
GND53: C107.2, C108.2, JP107.1, JP108.6, SJ162.1, U54.P$1, U54.P$7
GND54: C109.2, C110.2, JP109.1, JP110.6, SJ165.1, U55.P$1, U55.P$7
GND55: C111.2, C112.2, JP111.1, JP112.6, SJ168.1, U56.P$1, U56.P$7
GND56: C113.2, C114.2, JP113.1, JP114.6, SJ171.1, U57.P$1, U57.P$7
GND57: C115.2, C116.2, JP115.1, JP116.6, SJ174.1, U58.P$1, U58.P$7
GND58: C117.2, C118.2, JP117.1, JP118.6, SJ177.1, U59.P$1, U59.P$7
GND59: C119.2, C120.2, JP119.1, JP120.6, SJ180.1, U60.P$1, U60.P$7
GND60: C121.2, C122.2, JP121.1, JP122.6, SJ183.1, U61.P$1, U61.P$7
GND61: C123.2, C124.2, JP123.1, JP124.6, SJ186.1, U62.P$1, U62.P$7
GND62: C125.2, C126.2, JP125.1, JP126.6, SJ189.1, U63.P$1, U63.P$7
GND63: C127.2, C128.2, JP127.1, JP128.6, SJ192.1, U64.P$1, U64.P$7
GND64: C129.2, C130.2, JP129.1, JP130.6, SJ195.1, U65.P$1, U65.P$7
GND65: C131.2, C132.2, JP131.1, JP132.6, SJ198.1, U66.P$1, U66.P$7
GND66: C133.2, C134.2, JP133.1, JP134.6, SJ201.1, U67.P$1, U67.P$7
GND67: C135.2, C136.2, JP135.1, JP136.6, SJ204.1, U68.P$1, U68.P$7
GND68: C137.2, C138.2, JP137.1, JP138.6, SJ207.1, U69.P$1, U69.P$7
GND69: C139.2, C140.2, JP139.1, JP140.6, SJ210.1, U70.P$1, U70.P$7
GND70: C141.2, C142.2, JP141.1, JP142.6, SJ213.1, U71.P$1, U71.P$7
GND71: C143.2, C144.2, JP143.1, JP144.6, SJ216.1, U72.P$1, U72.P$7
GND72: C145.2, C146.2, JP145.1, JP146.6, SJ219.1, U73.P$1, U73.P$7
GND73: C147.2, C148.2, JP147.1, JP148.6, SJ222.1, U74.P$1, U74.P$7
GND74: C149.2, C150.2, JP149.1, JP150.6, SJ225.1, U75.P$1, U75.P$7
GND75: C151.2, C152.2, JP151.1, JP152.6, SJ228.1, U76.P$1, U76.P$7
GND76: C153.2, C154.2, JP153.1, JP154.6, SJ231.1, U77.P$1, U77.P$7
GND77: C155.2, C156.2, JP155.1, JP156.6, SJ234.1, U78.P$1, U78.P$7
GND78: C157.2, C158.2, JP157.1, JP158.6, SJ237.1, U79.P$1, U79.P$7
GND79: C159.2, C160.2, JP159.1, JP160.6, SJ240.1, U80.P$1, U80.P$7
GND80: C161.2, C162.2, JP161.1, JP162.6, SJ243.1, U81.P$1, U81.P$7
GND81: C163.2, C164.2, JP163.1, JP164.6, SJ246.1, U82.P$1, U82.P$7
GND82: C165.2, C166.2, JP165.1, JP166.6, SJ249.1, U83.P$1, U83.P$7
GND83: C167.2, C168.2, JP167.1, JP168.6, SJ252.1, U84.P$1, U84.P$7
GND84: C169.2, C170.2, JP169.1, JP170.6, SJ255.1, U85.P$1, U85.P$7
GND85: C171.2, C172.2, JP171.1, JP172.6, SJ258.1, U86.P$1, U86.P$7
GND86: C173.2, C174.2, JP173.1, JP174.6, SJ261.1, U87.P$1, U87.P$7
GND87: C175.2, C176.2, JP175.1, JP176.6, SJ264.1, U88.P$1, U88.P$7
GND88: C177.2, C178.2, JP177.1, JP178.6, SJ267.1, U89.P$1, U89.P$7
GND89: C179.2, C180.2, JP179.1, JP180.6, SJ270.1, U90.P$1, U90.P$7
GND90: C181.2, C182.2, JP181.1, JP182.6, SJ273.1, U91.P$1, U91.P$7
GND91: C183.2, C184.2, JP183.1, JP184.6, SJ276.1, U92.P$1, U92.P$7
GND92: C185.2, C186.2, JP185.1, JP186.6, SJ279.1, U93.P$1, U93.P$7
GND93: C187.2, C188.2, JP187.1, JP188.6, SJ282.1, U94.P$1, U94.P$7
GND94: C189.2, C190.2, JP189.1, JP190.6, SJ285.1, U95.P$1, U95.P$7
GND95: C191.2, C192.2, JP191.1, JP192.6, SJ288.1, U96.P$1, U96.P$7
GND96: C193.2, C194.2, JP193.1, JP194.6, SJ291.1, U97.P$1, U97.P$7
GND97: C195.2, C196.2, JP195.1, JP196.6, SJ294.1, U98.P$1, U98.P$7
GND98: C197.2, C198.2, JP197.1, JP198.6, SJ297.1, U99.P$1, U99.P$7
GND99: C199.2, C200.2, JP199.1, JP200.6, SJ300.1, U100.P$1, U100.P$7
unnamed: R1.2, SJ1.3
unnamed: R2.2, SJ1.1
unnamed: R3.2, SJ2.1
unnamed: R4.1, SJ3.3
unnamed: R5.2, SJ4.3
unnamed: R6.2, SJ4.1
unnamed: R7.2, SJ5.1
unnamed: R8.1, SJ6.3
unnamed: R9.2, SJ7.3
unnamed: R10.2, SJ7.1
unnamed: R11.2, SJ8.1
unnamed: R12.1, SJ9.3
unnamed: R13.2, SJ10.3
unnamed: R14.2, SJ10.1
unnamed: R15.2, SJ11.1
unnamed: R16.1, SJ12.3
unnamed: R17.2, SJ13.3
unnamed: R18.2, SJ13.1
unnamed: R19.2, SJ14.1
unnamed: R20.1, SJ15.3
unnamed: R21.2, SJ16.3
unnamed: R22.2, SJ16.1
unnamed: R23.2, SJ17.1
unnamed: R24.1, SJ18.3
unnamed: R25.2, SJ19.3
unnamed: R26.2, SJ19.1
unnamed: R27.2, SJ20.1
unnamed: R28.1, SJ21.3
unnamed: R29.2, SJ22.3
unnamed: R30.2, SJ22.1
unnamed: R31.2, SJ23.1
unnamed: R32.1, SJ24.3
unnamed: R33.2, SJ25.3
unnamed: R34.2, SJ25.1
unnamed: R35.2, SJ26.1
unnamed: R36.1, SJ27.3
unnamed: R37.2, SJ28.3
unnamed: R38.2, SJ28.1
unnamed: R39.2, SJ29.1
unnamed: R40.1, SJ30.3
unnamed: R41.2, SJ31.3
unnamed: R42.2, SJ31.1
unnamed: R43.2, SJ32.1
unnamed: R44.1, SJ33.3
unnamed: R45.2, SJ34.3
unnamed: R46.2, SJ34.1
unnamed: R47.2, SJ35.1
unnamed: R48.1, SJ36.3
unnamed: R49.2, SJ37.3
unnamed: R50.2, SJ37.1
unnamed: R51.2, SJ38.1
unnamed: R52.1, SJ39.3
unnamed: R53.2, SJ40.3
unnamed: R54.2, SJ40.1
unnamed: R55.2, SJ41.1
unnamed: R56.1, SJ42.3
unnamed: R57.2, SJ43.3
unnamed: R58.2, SJ43.1
unnamed: R59.2, SJ44.1
unnamed: R60.1, SJ45.3
unnamed: R61.2, SJ46.3
unnamed: R62.2, SJ46.1
unnamed: R63.2, SJ47.1
unnamed: R64.1, SJ48.3
unnamed: R65.2, SJ49.3
unnamed: R66.2, SJ49.1
unnamed: R67.2, SJ50.1
unnamed: R68.1, SJ51.3
unnamed: R69.2, SJ52.3
unnamed: R70.2, SJ52.1
unnamed: R71.2, SJ53.1
unnamed: R72.1, SJ54.3
unnamed: R73.2, SJ55.3
unnamed: R74.2, SJ55.1
unnamed: R75.2, SJ56.1
unnamed: R76.1, SJ57.3
unnamed: R77.2, SJ58.3
unnamed: R78.2, SJ58.1
unnamed: R79.2, SJ59.1
unnamed: R80.1, SJ60.3
unnamed: R81.2, SJ61.3
unnamed: R82.2, SJ61.1
unnamed: R83.2, SJ62.1
unnamed: R84.1, SJ63.3
unnamed: R85.2, SJ64.3
unnamed: R86.2, SJ64.1
unnamed: R87.2, SJ65.1
unnamed: R88.1, SJ66.3
unnamed: R89.2, SJ67.3
unnamed: R90.2, SJ67.1
unnamed: R91.2, SJ68.1
unnamed: R92.1, SJ69.3
unnamed: R93.2, SJ70.3
unnamed: R94.2, SJ70.1
unnamed: R95.2, SJ71.1
unnamed: R96.1, SJ72.3
unnamed: R97.2, SJ73.3
unnamed: R98.2, SJ73.1
unnamed: R99.2, SJ74.1
unnamed: R100.1, SJ75.3
unnamed: R101.2, SJ76.3
unnamed: R102.2, SJ76.1
unnamed: R103.2, SJ77.1
unnamed: R104.1, SJ78.3
unnamed: R105.2, SJ79.3
unnamed: R106.2, SJ79.1
unnamed: R107.2, SJ80.1
unnamed: R108.1, SJ81.3
unnamed: R109.2, SJ82.3
unnamed: R110.2, SJ82.1
unnamed: R111.2, SJ83.1
unnamed: R112.1, SJ84.3
unnamed: R113.2, SJ85.3
unnamed: R114.2, SJ85.1
unnamed: R115.2, SJ86.1
unnamed: R116.1, SJ87.3
unnamed: R117.2, SJ88.3
unnamed: R118.2, SJ88.1
unnamed: R119.2, SJ89.1
unnamed: R120.1, SJ90.3
unnamed: R121.2, SJ91.3
unnamed: R122.2, SJ91.1
unnamed: R123.2, SJ92.1
unnamed: R124.1, SJ93.3
unnamed: R125.2, SJ94.3
unnamed: R126.2, SJ94.1
unnamed: R127.2, SJ95.1
unnamed: R128.1, SJ96.3
unnamed: R129.2, SJ97.3
unnamed: R130.2, SJ97.1
unnamed: R131.2, SJ98.1
unnamed: R132.1, SJ99.3
unnamed: R133.2, SJ100.3
unnamed: R134.2, SJ100.1
unnamed: R135.2, SJ101.1
unnamed: R136.1, SJ102.3
unnamed: R137.2, SJ103.3
unnamed: R138.2, SJ103.1
unnamed: R139.2, SJ104.1
unnamed: R140.1, SJ105.3
unnamed: R141.2, SJ106.3
unnamed: R142.2, SJ106.1
unnamed: R143.2, SJ107.1
unnamed: R144.1, SJ108.3
unnamed: R145.2, SJ109.3
unnamed: R146.2, SJ109.1
unnamed: R147.2, SJ110.1
unnamed: R148.1, SJ111.3
unnamed: R149.2, SJ112.3
unnamed: R150.2, SJ112.1
unnamed: R151.2, SJ113.1
unnamed: R152.1, SJ114.3
unnamed: R153.2, SJ115.3
unnamed: R154.2, SJ115.1
unnamed: R155.2, SJ116.1
unnamed: R156.1, SJ117.3
unnamed: R157.2, SJ118.3
unnamed: R158.2, SJ118.1
unnamed: R159.2, SJ119.1
unnamed: R160.1, SJ120.3
unnamed: R161.2, SJ121.3
unnamed: R162.2, SJ121.1
unnamed: R163.2, SJ122.1
unnamed: R164.1, SJ123.3
unnamed: R165.2, SJ124.3
unnamed: R166.2, SJ124.1
unnamed: R167.2, SJ125.1
unnamed: R168.1, SJ126.3
unnamed: R169.2, SJ127.3
unnamed: R170.2, SJ127.1
unnamed: R171.2, SJ128.1
unnamed: R172.1, SJ129.3
unnamed: R173.2, SJ130.3
unnamed: R174.2, SJ130.1
unnamed: R175.2, SJ131.1
unnamed: R176.1, SJ132.3
unnamed: R177.2, SJ133.3
unnamed: R178.2, SJ133.1
unnamed: R179.2, SJ134.1
unnamed: R180.1, SJ135.3
unnamed: R181.2, SJ136.3
unnamed: R182.2, SJ136.1
unnamed: R183.2, SJ137.1
unnamed: R184.1, SJ138.3
unnamed: R185.2, SJ139.3
unnamed: R186.2, SJ139.1
unnamed: R187.2, SJ140.1
unnamed: R188.1, SJ141.3
unnamed: R189.2, SJ142.3
unnamed: R190.2, SJ142.1
unnamed: R191.2, SJ143.1
unnamed: R192.1, SJ144.3
unnamed: R193.2, SJ145.3
unnamed: R194.2, SJ145.1
unnamed: R195.2, SJ146.1
unnamed: R196.1, SJ147.3
unnamed: R197.2, SJ148.3
unnamed: R198.2, SJ148.1
unnamed: R199.2, SJ149.1
unnamed: R200.1, SJ150.3
unnamed: R201.2, SJ151.3
unnamed: R202.2, SJ151.1
unnamed: R203.2, SJ152.1
unnamed: R204.1, SJ153.3
unnamed: R205.2, SJ154.3
unnamed: R206.2, SJ154.1
unnamed: R207.2, SJ155.1
unnamed: R208.1, SJ156.3
unnamed: R209.2, SJ157.3
unnamed: R210.2, SJ157.1
unnamed: R211.2, SJ158.1
unnamed: R212.1, SJ159.3
unnamed: R213.2, SJ160.3
unnamed: R214.2, SJ160.1
unnamed: R215.2, SJ161.1
unnamed: R216.1, SJ162.3
unnamed: R217.2, SJ163.3
unnamed: R218.2, SJ163.1
unnamed: R219.2, SJ164.1
unnamed: R220.1, SJ165.3
unnamed: R221.2, SJ166.3
unnamed: R222.2, SJ166.1
unnamed: R223.2, SJ167.1
unnamed: R224.1, SJ168.3
unnamed: R225.2, SJ169.3
unnamed: R226.2, SJ169.1
unnamed: R227.2, SJ170.1
unnamed: R228.1, SJ171.3
unnamed: R229.2, SJ172.3
unnamed: R230.2, SJ172.1
unnamed: R231.2, SJ173.1
unnamed: R232.1, SJ174.3
unnamed: R233.2, SJ175.3
unnamed: R234.2, SJ175.1
unnamed: R235.2, SJ176.1
unnamed: R236.1, SJ177.3
unnamed: R237.2, SJ178.3
unnamed: R238.2, SJ178.1
unnamed: R239.2, SJ179.1
unnamed: R240.1, SJ180.3
unnamed: R241.2, SJ181.3
unnamed: R242.2, SJ181.1
unnamed: R243.2, SJ182.1
unnamed: R244.1, SJ183.3
unnamed: R245.2, SJ184.3
unnamed: R246.2, SJ184.1
unnamed: R247.2, SJ185.1
unnamed: R248.1, SJ186.3
unnamed: R249.2, SJ187.3
unnamed: R250.2, SJ187.1
unnamed: R251.2, SJ188.1
unnamed: R252.1, SJ189.3
unnamed: R253.2, SJ190.3
unnamed: R254.2, SJ190.1
unnamed: R255.2, SJ191.1
unnamed: R256.1, SJ192.3
unnamed: R257.2, SJ193.3
unnamed: R258.2, SJ193.1
unnamed: R259.2, SJ194.1
unnamed: R260.1, SJ195.3
unnamed: R261.2, SJ196.3
unnamed: R262.2, SJ196.1
unnamed: R263.2, SJ197.1
unnamed: R264.1, SJ198.3
unnamed: R265.2, SJ199.3
unnamed: R266.2, SJ199.1
unnamed: R267.2, SJ200.1
unnamed: R268.1, SJ201.3
unnamed: R269.2, SJ202.3
unnamed: R270.2, SJ202.1
unnamed: R271.2, SJ203.1
unnamed: R272.1, SJ204.3
unnamed: R273.2, SJ205.3
unnamed: R274.2, SJ205.1
unnamed: R275.2, SJ206.1
unnamed: R276.1, SJ207.3
unnamed: R277.2, SJ208.3
unnamed: R278.2, SJ208.1
unnamed: R279.2, SJ209.1
unnamed: R280.1, SJ210.3
unnamed: R281.2, SJ211.3
unnamed: R282.2, SJ211.1
unnamed: R283.2, SJ212.1
unnamed: R284.1, SJ213.3
unnamed: R285.2, SJ214.3
unnamed: R286.2, SJ214.1
unnamed: R287.2, SJ215.1
unnamed: R288.1, SJ216.3
unnamed: R289.2, SJ217.3
unnamed: R290.2, SJ217.1
unnamed: R291.2, SJ218.1
unnamed: R292.1, SJ219.3
unnamed: R293.2, SJ220.3
unnamed: R294.2, SJ220.1
unnamed: R295.2, SJ221.1
unnamed: R296.1, SJ222.3
unnamed: R297.2, SJ223.3
unnamed: R298.2, SJ223.1
unnamed: R299.2, SJ224.1
unnamed: R300.1, SJ225.3
unnamed: R301.2, SJ226.3
unnamed: R302.2, SJ226.1
unnamed: R303.2, SJ227.1
unnamed: R304.1, SJ228.3
unnamed: R305.2, SJ229.3
unnamed: R306.2, SJ229.1
unnamed: R307.2, SJ230.1
unnamed: R308.1, SJ231.3
unnamed: R309.2, SJ232.3
unnamed: R310.2, SJ232.1
unnamed: R311.2, SJ233.1
unnamed: R312.1, SJ234.3
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
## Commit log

2015-06-29 Made component and schematic
2015-06-30 Pre-checklist commit
2015-06-30 ready for QC check
2015-07-01 Set isolate to 8 mil, added note
2015-08-01 First working example, i2c and spi
2015-08-03 Rev 0.2
2015-08-03 Rev 0.2, DRC fixed
2015-08-03 Ready for review
2015-08-04 fixed oversized via
2015-08-21 Documented test
2015-08-24 incremented version number
2015-08-24 Renamed boardfiles
2015-08-27 created panel v10
2015-10-21 Updated readme and directories
2015-10-21 pushing final changes for review
2015-10-21 Squashed 'Libraries/Arduino/' content from commit 373d5cd
    git-subtree-dir: Libraries/Arduino
    git-subtree-split: 373d5cd170aab532a42016c9282187b3efea6f02
2015-11-11 Added fritzing diagram
2016-01-21 Moved File
    Moved to Fritzing_Parts
2016-09-24 Added correction for temperature sensor
2016-12-12 Pointed to new arduino library
2016-12-12 Squashed 'Libraries/Arduino/' changes from 9f6cbfb..d682b05
    3f71ec2 Updated documentation to reflect new pull
    fab9475 Merge pull request #5 from JamesWebb73/fix-float-precision
    c686b2c changed to divide return values
    git-subtree-dir: Libraries/Arduino
    git-subtree-split: d682b05838161ac95107d8356bb2c123ad7f4811
2016-12-12 Fixed update command example
2018-10-21 Added dew point function and some more pressure functions
2018-10-21 comments
2018-10-21 More Comments
2018-11-04 Removing library from repo.
    The library for this board is over here: https://github.com/sparkfun/SparkFun_BME280_Arduino_Library
2020-03-05 Update README
    Deleting mention of Library as part of repository contents.
